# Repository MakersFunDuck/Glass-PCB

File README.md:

# Glass-PCB
Hardware files and blink code for the experimental Glass breakout board

This is the Kicad files for the glass breakout board which has famous "10 cent MCU". I used CH32V003AxMx version. To upload the firmware to the board, you need to install 'Mounriver studio'  from http://www.mounriver.com/ for free. Also you need to have one of their debuggers like this one: (https://s.click.aliexpress.com/e/_EwrcMk1)

You can also upload the code using arduino uno or esp board, but I have not tried that.

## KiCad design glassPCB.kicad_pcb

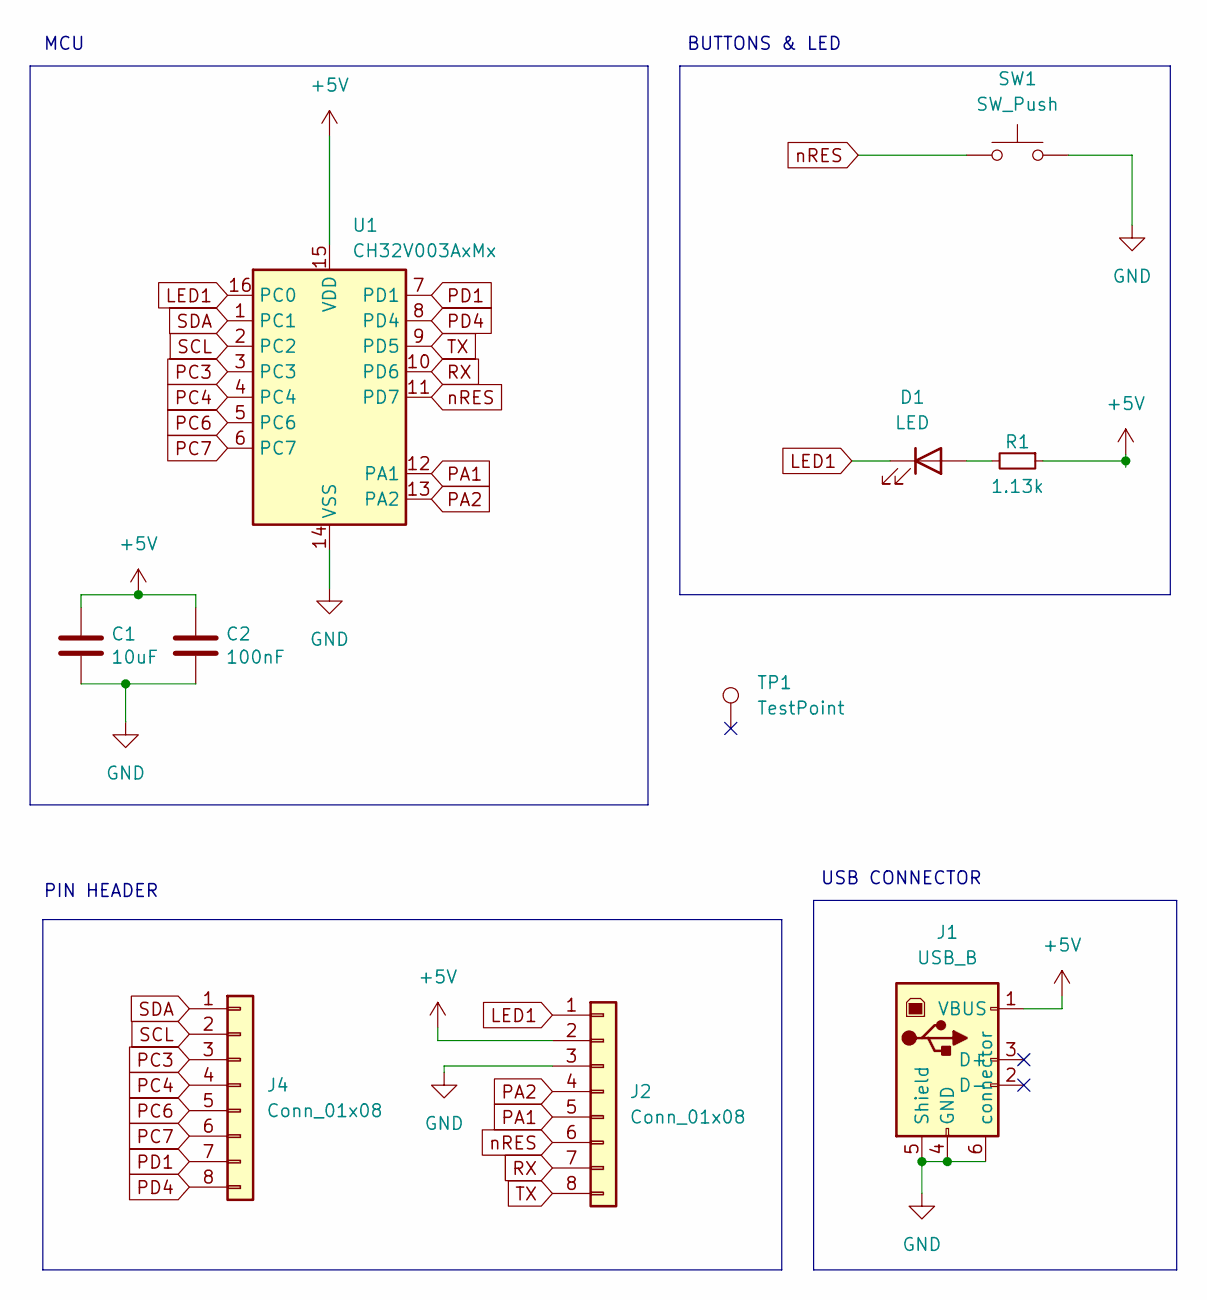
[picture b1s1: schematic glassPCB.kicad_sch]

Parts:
C1: 10uF; C_0402_1005Metric_Pad0.74x0.62mm_HandSolder
C2: 100nF; C_0402_1005Metric_Pad0.74x0.62mm_HandSolder
D1: LED; LED_0402_1005Metric_Pad0.77x0.64mm_HandSolder; LCSC Part # C965794
J1: USB_B; USB_Micro-B_Molex_47346-0001
J2, J4: Conn_01x08; PIN_HEADER
R1: 1.13k; R_0402_1005Metric_Pad0.72x0.64mm_HandSolder; LCSC Part # C3016053
SW1: SW_Push; SW_SPST_TL3342; LCSC Part # C2874210
TP1: TestPoint; duck
U1: CH32V003AxMx; SOP-16_3.9x9.9mm_P1.27mm

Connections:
+5V: C1.1, C2.1, J1.1 (VBUS), J2.2, R1.1, U1.15 (VDD)
GND: C1.2, C2.2, J1.4 (GND), J1.5 (Shield), J1.6 (connector), J2.3, SW1.2, U1.14 (VSS)
LED1: D1.1 (K), J2.1, U1.16 (PC0)
unnamed: D1.2 (A), R1.2
PA1: J2.5, U1.12 (PA1)
PA2: J2.4, U1.13 (PA2)
PC3: J4.3, U1.3 (PC3)
PC4: J4.4, U1.4 (PC4)
PC6: J4.5, U1.5 (PC6)
PC7: J4.6, U1.6 (PC7)
PD1: J4.7, U1.7 (PD1)
PD4: J4.8, U1.8 (PD4)
RX: J2.7, U1.10 (PD6)
SCL: J4.2, U1.2 (PC2)
SDA: J4.1, U1.1 (PC1)
TX: J2.8, U1.9 (PD5)
nRES: J2.6, SW1.1, U1.11 (PD7)

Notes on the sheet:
PIN HEADER
BUTTONS & LED
MCU
USB CONNECTOR

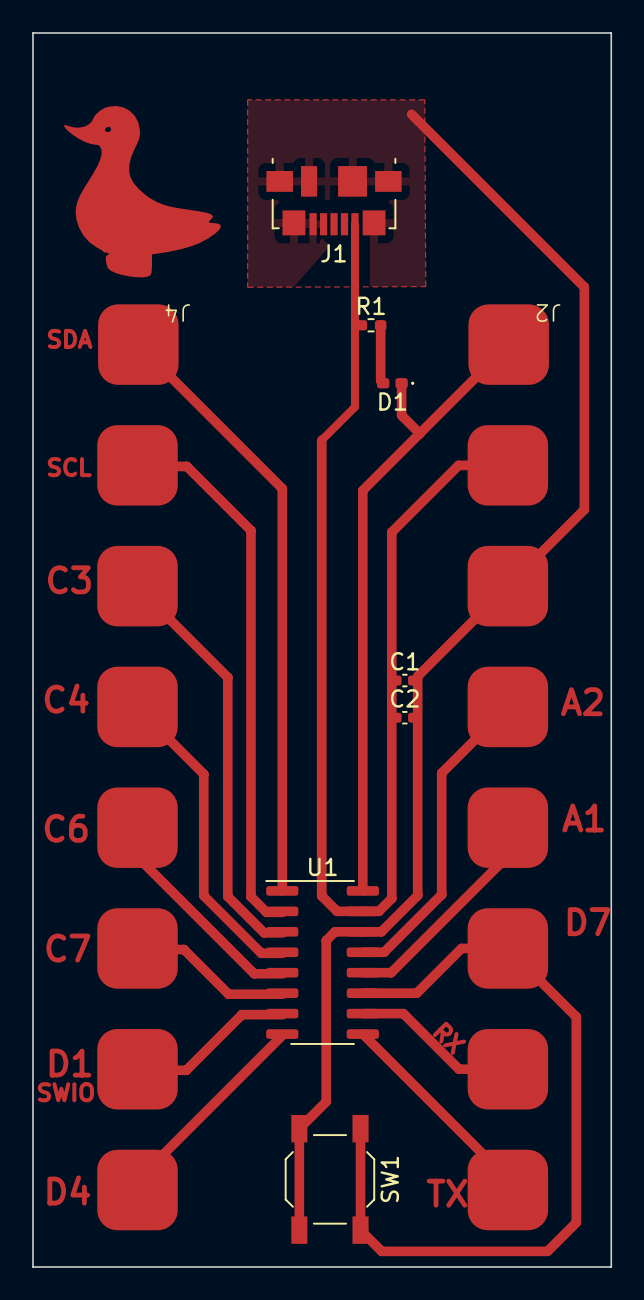
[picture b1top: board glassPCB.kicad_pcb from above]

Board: 2 copper layers, 35.9 x 76.6 mm, 10 parts (0 on the bottom side), 17 nets.
